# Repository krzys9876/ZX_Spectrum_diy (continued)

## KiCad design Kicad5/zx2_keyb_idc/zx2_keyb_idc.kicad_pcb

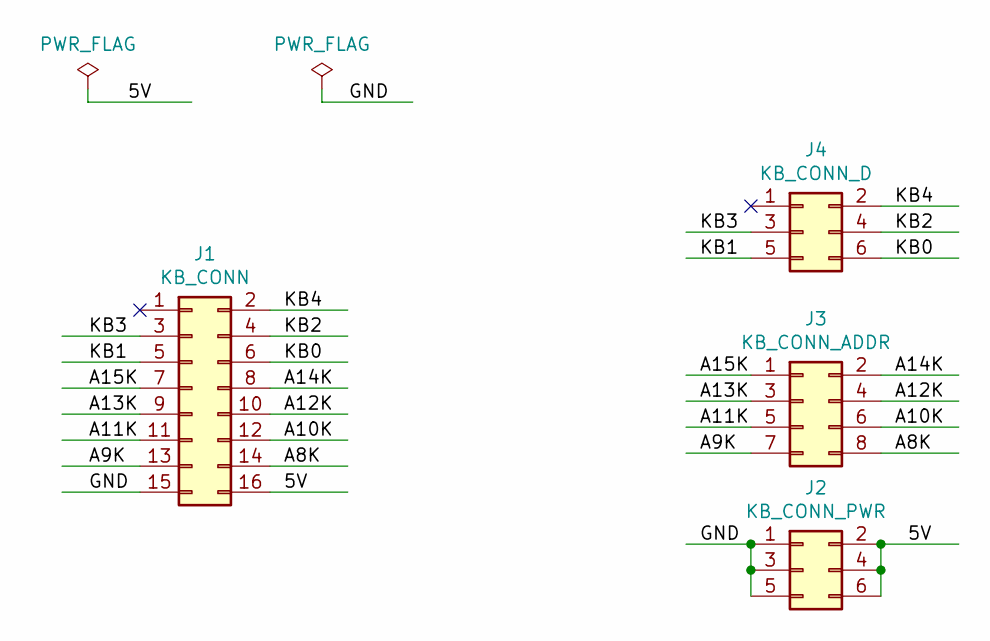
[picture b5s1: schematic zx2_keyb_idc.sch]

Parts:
J1: KB_CONN; PinHeader_2x08_P2.54mm_Vertical_SMD
J2: KB_CONN_PWR; PinHeader_2x03_P2.54mm_Vertical
J3: KB_CONN_ADDR; PinHeader_2x04_P2.54mm_Vertical
J4: KB_CONN_D; PinHeader_2x03_P2.54mm_Vertical

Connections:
/5V: J1.16, J2.2, J2.4, J2.6
/A8K: J1.14, J3.8
/A9K: J1.13, J3.7
/A10K: J1.12, J3.6
/A11K: J1.11, J3.5
/A12K: J1.10, J3.4
/A13K: J1.9, J3.3
/A14K: J1.8, J3.2
/A15K: J1.7, J3.1
/GND: J1.15, J2.1, J2.3, J2.5
/KB0: J1.6, J4.6
/KB1: J1.5, J4.5
/KB2: J1.4, J4.4
/KB3: J1.3, J4.3
/KB4: J1.2, J4.2

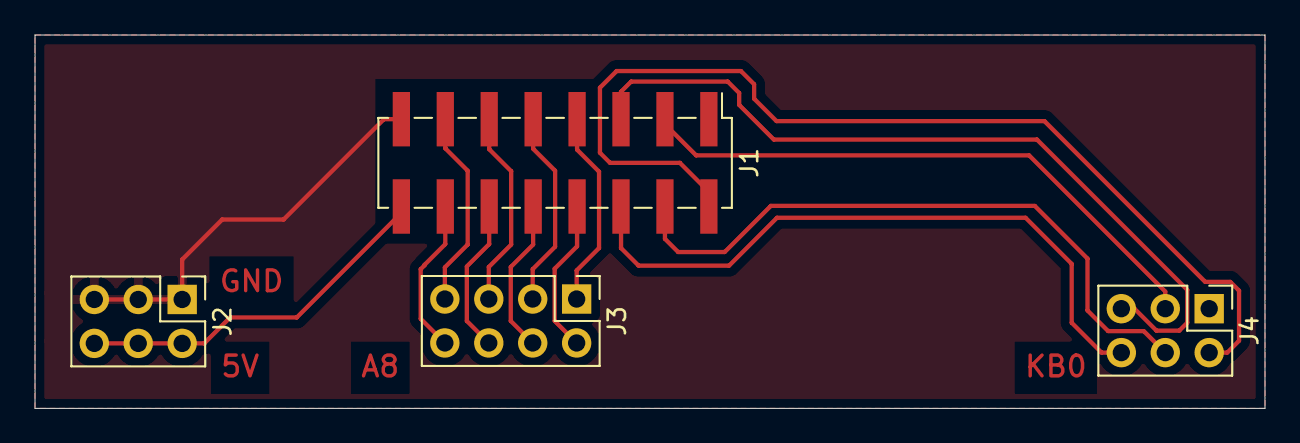
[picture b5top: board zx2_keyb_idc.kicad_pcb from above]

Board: 2 copper layers, 71.1 x 21.6 mm, 4 parts (0 on the bottom side), 15 nets.

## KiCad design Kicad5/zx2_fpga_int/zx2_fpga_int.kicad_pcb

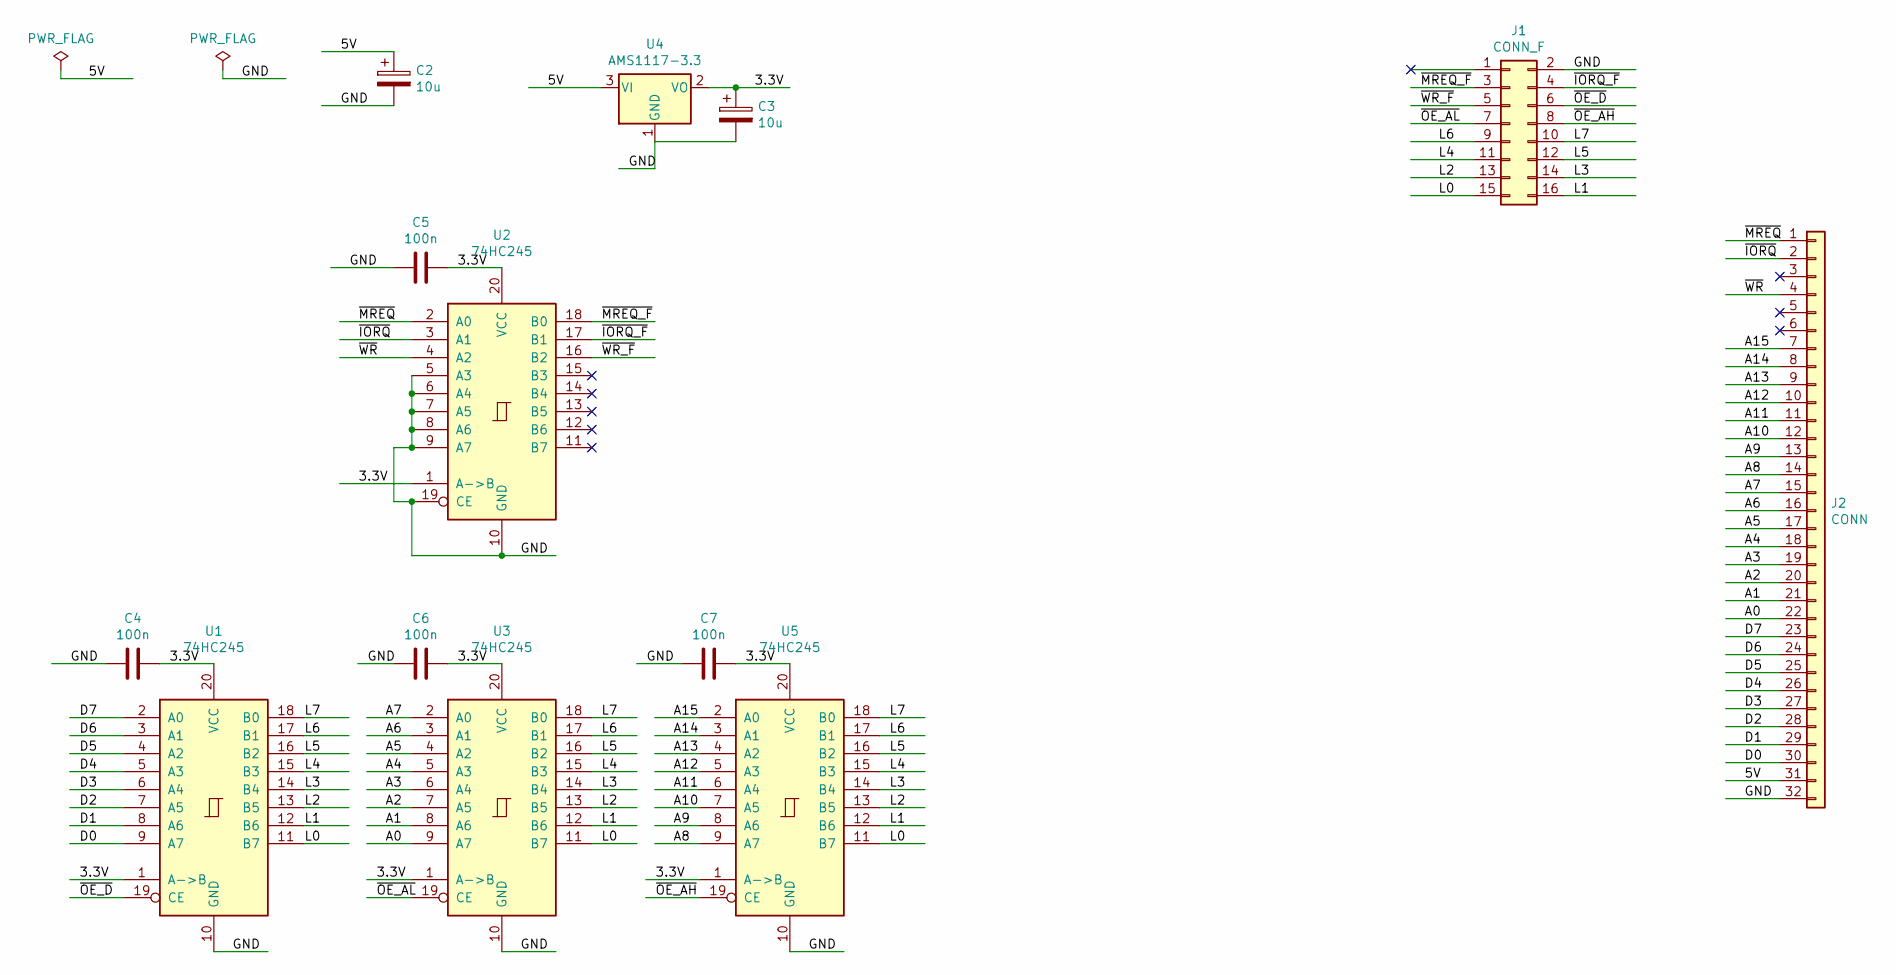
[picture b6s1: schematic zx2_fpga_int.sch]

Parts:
C2, C3: 10u; C_1210_3225Metric
C4, C5, C6, C7: 100n; C_1206_3216Metric
J1: CONN_F; PinHeader_2x08_P2.54mm_Vertical
J2: CONN; PinHeader_1x32_P2.54mm_Horizontal
U1, U2, U3, U5: 74HC245; SO-20_12.8x7.5mm_P1.27mm
U4: AMS1117-3.3; SOT-223-3_TabPin2

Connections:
/3.3V: C3.1, C4.1, C5.1, C6.1, C7.1, U1.1 (A->B), U1.20 (VCC), U2.1 (A->B), U2.20 (VCC), U3.1 (A->B), U3.20 (VCC), U4.2 (VO), U5.1 (A->B), U5.20 (VCC)
/5V: C2.1, J2.31, U4.3 (VI)
/A0: J2.22, U3.9 (A7)
/A1: J2.21, U3.8 (A6)
/A2: J2.20, U3.7 (A5)
/A3: J2.19, U3.6 (A4)
/A4: J2.18, U3.5 (A3)
/A5: J2.17, U3.4 (A2)
/A6: J2.16, U3.3 (A1)
/A7: J2.15, U3.2 (A0)
/A8: J2.14, U5.9 (A7)
/A9: J2.13, U5.8 (A6)
/A10: J2.12, U5.7 (A5)
/A11: J2.11, U5.6 (A4)
/A12: J2.10, U5.5 (A3)
/A13: J2.9, U5.4 (A2)
/A14: J2.8, U5.3 (A1)
/A15: J2.7, U5.2 (A0)
/D0: J2.30, U1.9 (A7)
/D1: J2.29, U1.8 (A6)
/D2: J2.28, U1.7 (A5)
/D3: J2.27, U1.6 (A4)
/D4: J2.26, U1.5 (A3)
/D5: J2.25, U1.4 (A2)
/D6: J2.24, U1.3 (A1)
/D7: J2.23, U1.2 (A0)
/GND: C2.2, C3.2, C4.2, C5.2, C6.2, C7.2, J1.2, J2.32, U1.10 (GND), U2.5 (A3), U2.6 (A4), U2.7 (A5), U2.8 (A6), U2.9 (A7), U2.10 (GND), U2.19 (CE), U3.10 (GND), U4.1 (GND), U5.10 (GND)
/L0: J1.15, U1.11 (B7), U3.11 (B7), U5.11 (B7)
/L1: J1.16, U1.12 (B6), U3.12 (B6), U5.12 (B6)
/L2: J1.13, U1.13 (B5), U3.13 (B5), U5.13 (B5)
/L3: J1.14, U1.14 (B4), U3.14 (B4), U5.14 (B4)
/L4: J1.11, U1.15 (B3), U3.15 (B3), U5.15 (B3)
/L5: J1.12, U1.16 (B2), U3.16 (B2), U5.16 (B2)
/L6: J1.9, U1.17 (B1), U3.17 (B1), U5.17 (B1)
/L7: J1.10, U1.18 (B0), U3.18 (B0), U5.18 (B0)
/~IORQ: J2.2, U2.3 (A1)
/~IORQ_F: J1.4, U2.17 (B1)
/~MREQ: J2.1, U2.2 (A0)
/~MREQ_F: J1.3, U2.18 (B0)
/~OE_AH: J1.8, U5.19 (CE)
/~OE_AL: J1.7, U3.19 (CE)
/~OE_D: J1.6, U1.19 (CE)
/~WR: J2.4, U2.4 (A2)
/~WR_F: J1.5, U2.16 (B2)

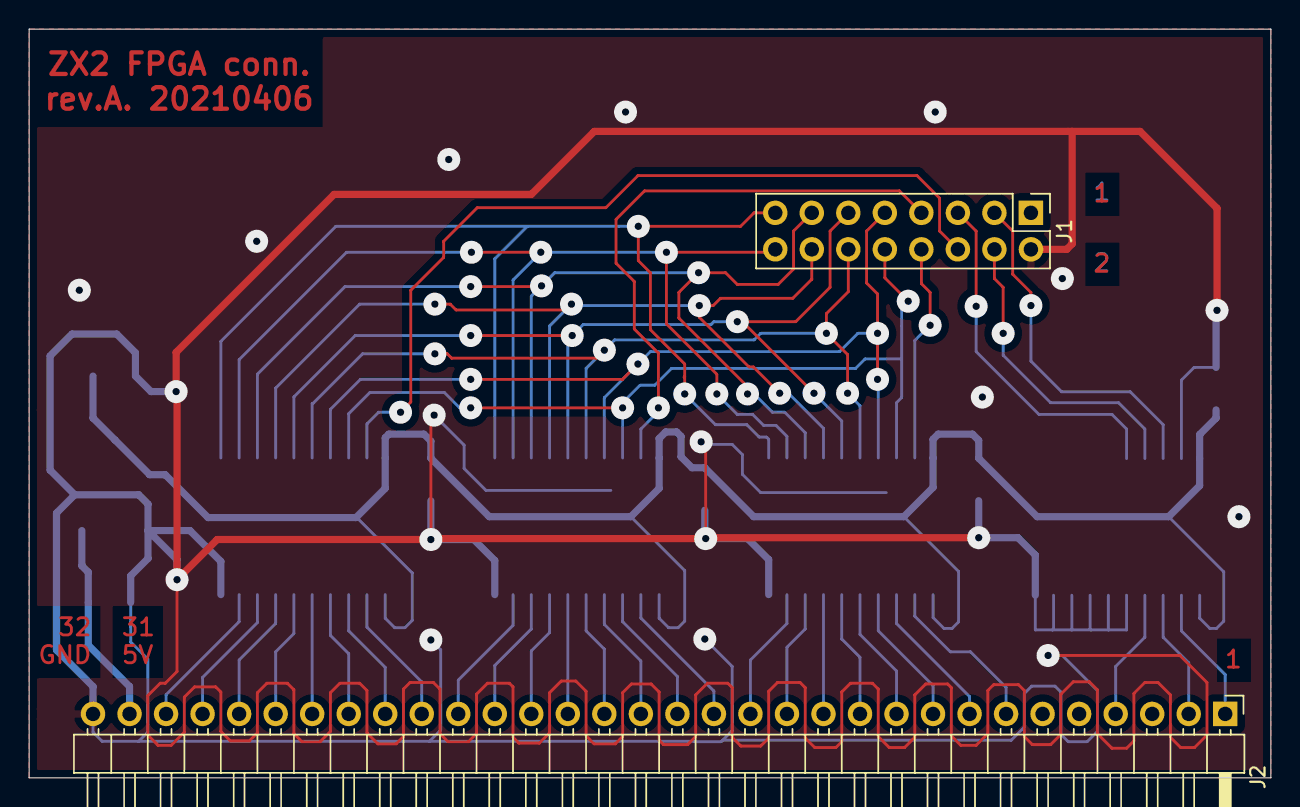
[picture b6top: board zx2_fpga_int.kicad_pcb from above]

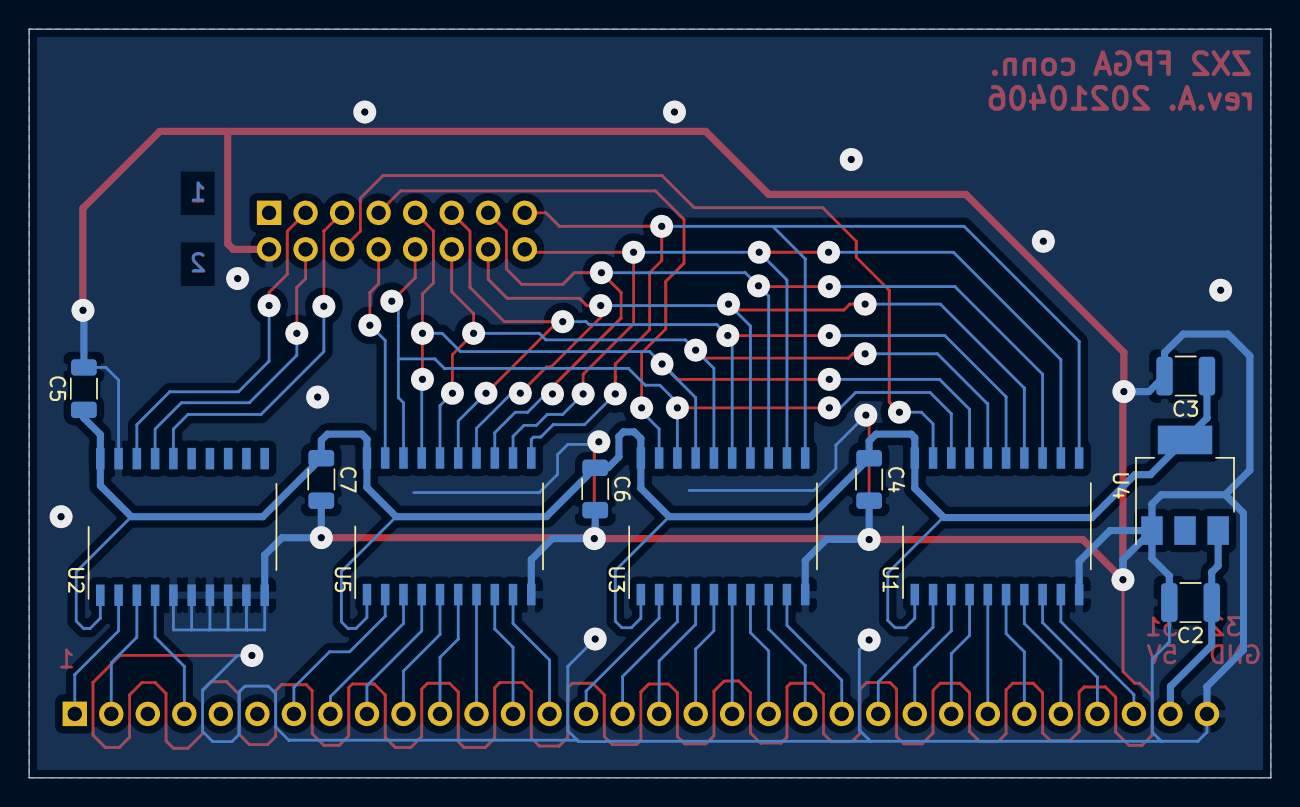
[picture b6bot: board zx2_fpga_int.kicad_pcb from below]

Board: 2 copper layers, 86.4 x 52.1 mm, 13 parts (11 on the bottom side), 44 nets.

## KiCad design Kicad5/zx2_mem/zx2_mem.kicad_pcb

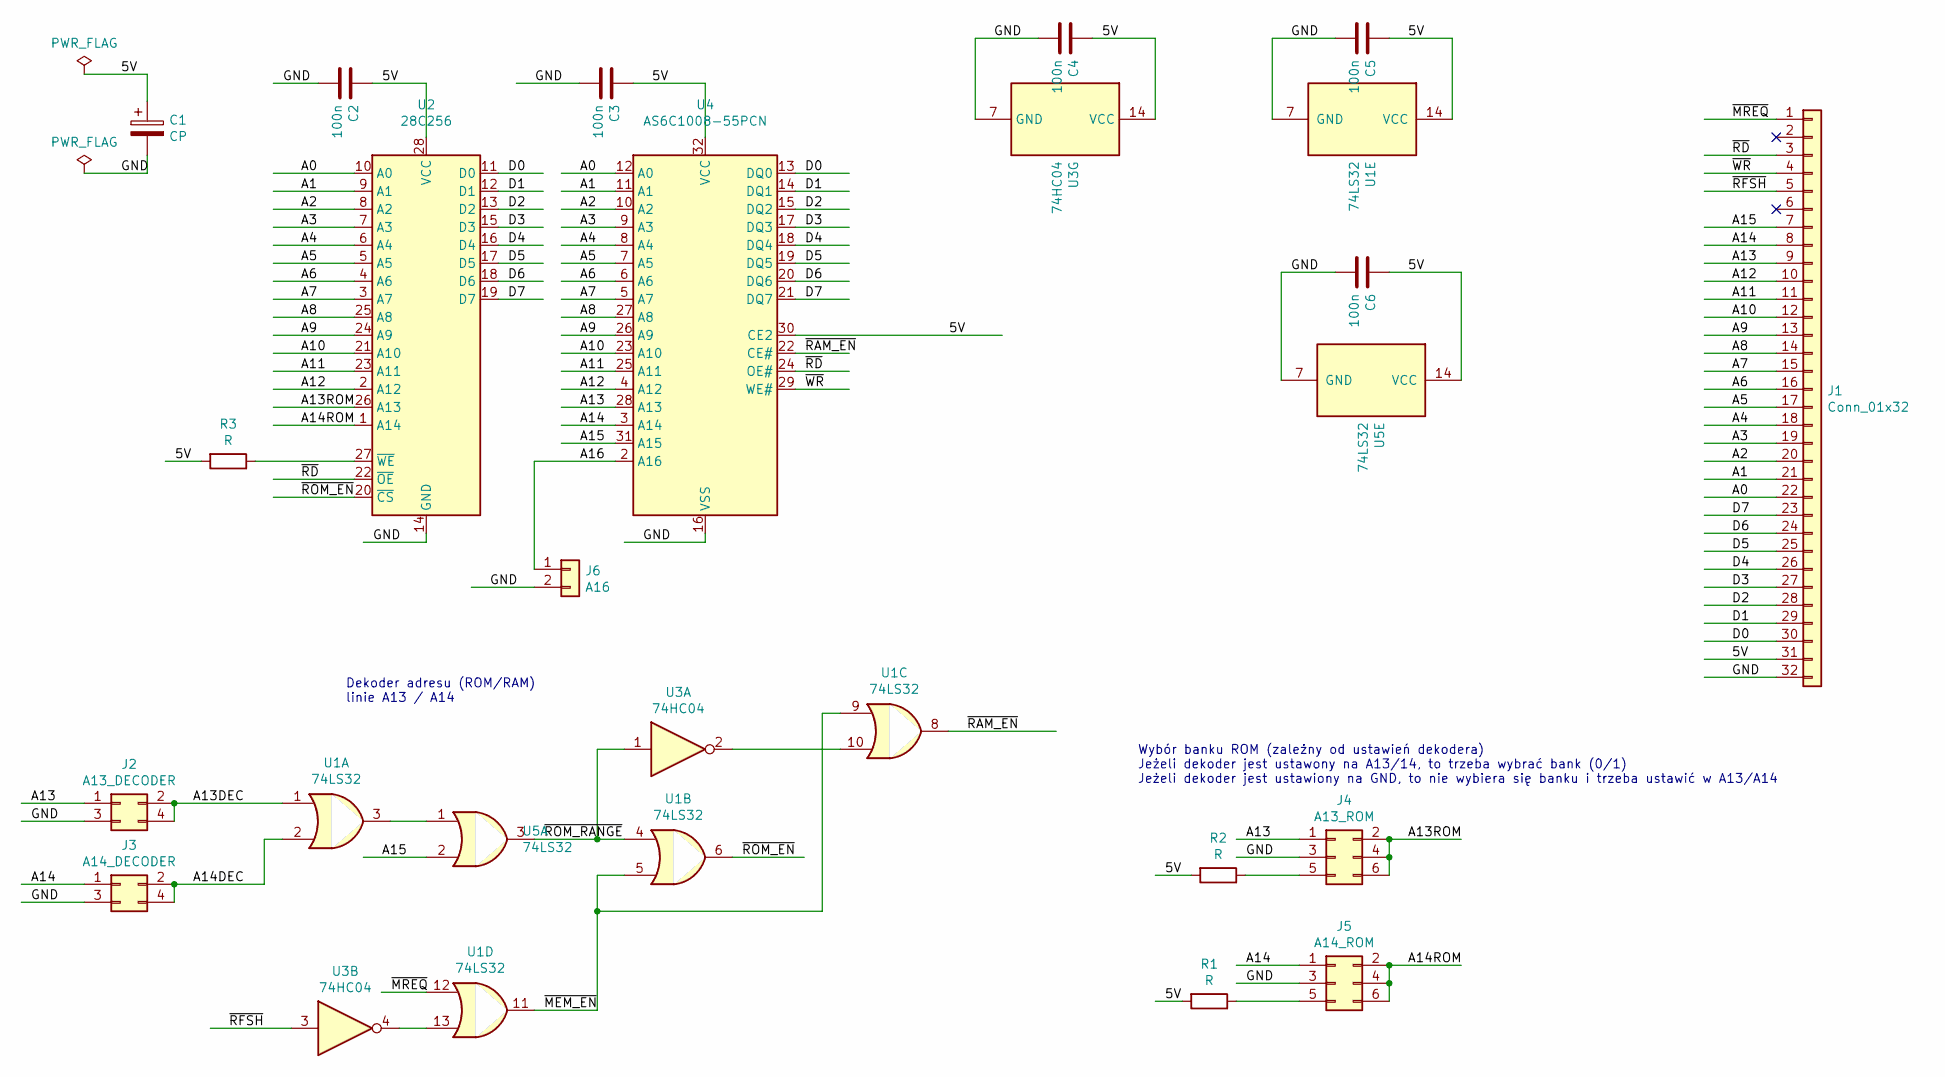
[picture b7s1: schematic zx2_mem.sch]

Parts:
C1: CP; C_1210_3225Metric
C2, C3, C4, C5, C6: 100n; C_1206_3216Metric
J1: Conn_01x32; PinHeader_1x32_P2.54mm_Horizontal
J2: A13_DECODER; PinHeader_2x02_P2.54mm_Vertical
J3: A14_DECODER; PinHeader_2x02_P2.54mm_Vertical
J4: A13_ROM; PinHeader_2x03_P2.54mm_Vertical
J5: A14_ROM; PinHeader_2x03_P2.54mm_Vertical
J6: A16; PinHeader_1x02_P2.54mm_Vertical
R1, R2, R3: R; R_0805_2012Metric
U1, U5: 74LS32; DIP-14_W7.62mm
U2: 28C256; DIP-28_W15.24mm
U3: 74HC04; DIP-14_W7.62mm
U4: AS6C1008-55PCN; DIP-32_W15.24mm

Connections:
/5V: C1.1, C2.1, C3.1, C4.1, C5.1, C6.1, J1.31, R1.2, R2.2, R3.2, U1.14 (VCC), U2.28 (VCC), U3.14 (VCC), U4.30 (CE2), U4.32 (VCC), U5.14 (VCC)
/A0: J1.22, U2.10 (A0), U4.12 (A0)
/A1: J1.21, U2.9 (A1), U4.11 (A1)
/A2: J1.20, U2.8 (A2), U4.10 (A2)
/A3: J1.19, U2.7 (A3), U4.9 (A3)
/A4: J1.18, U2.6 (A4), U4.8 (A4)
/A5: J1.17, U2.5 (A5), U4.7 (A5)
/A6: J1.16, U2.4 (A6), U4.6 (A6)
/A7: J1.15, U2.3 (A7), U4.5 (A7)
/A8: J1.14, U2.25 (A8), U4.27 (A8)
/A9: J1.13, U2.24 (A9), U4.26 (A9)
/A10: J1.12, U2.21 (A10), U4.23 (A10)
/A11: J1.11, U2.23 (A11), U4.25 (A11)
/A12: J1.10, U2.2 (A12), U4.4 (A12)
/A13: J1.9, J2.1, J4.1, U4.28 (A13)
/A13DEC: J2.2, J2.4, U1.1
/A13ROM: J4.2, J4.4, J4.6, U2.26 (A13)
/A14: J1.8, J3.1, J5.1, U4.3 (A14)
/A14DEC: J3.2, J3.4, U1.2
/A14ROM: J5.2, J5.4, J5.6, U2.1 (A14)
/A15: J1.7, U4.31 (A15), U5.2
/A16: J6.1, U4.2 (A16)
/D0: J1.30, U2.11 (D0), U4.13 (DQ0)
/D1: J1.29, U2.12 (D1), U4.14 (DQ1)
/D2: J1.28, U2.13 (D2), U4.15 (DQ2)
/D3: J1.27, U2.15 (D3), U4.17 (DQ3)
/D4: J1.26, U2.16 (D4), U4.18 (DQ4)
/D5: J1.25, U2.17 (D5), U4.19 (DQ5)
/D6: J1.24, U2.18 (D6), U4.20 (DQ6)
/D7: J1.23, U2.19 (D7), U4.21 (DQ7)
/GND: C1.2, C2.2, C3.2, C4.2, C5.2, C6.2, J1.32, J2.3, J3.3, J4.3, J5.3, J6.2, U1.7 (GND), U2.14 (GND), U3.7 (GND), U4.16 (VSS), U5.7 (GND)
/~MEM_EN: U1.5, U1.9, U1.11
/~MREQ: J1.1, U1.12
/~RAM_EN: U1.8, U4.22 (CE#)
/~RD: J1.3, U2.22 (~OE), U4.24 (OE#)
/~RFSH: J1.5, U3.3
/~ROM_EN: U1.6, U2.20 (~CS)
/~ROM_RANGE: U1.4, U3.1, U5.3
/~WR: J1.4, U4.29 (WE#)
unnamed: J4.5, R2.1
unnamed: J5.5, R1.1
unnamed: R3.1, U2.27 (~WE)
unnamed: U1.3, U5.1
unnamed: U1.10, U3.2
unnamed: U1.13, U3.4

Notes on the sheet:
Dekoder adresu (ROM/RAM) linie A13 / A14
Wybór banku ROM (zależny od ustawień dekodera) Jeżeli dekoder jest ustawony na A13/14, to trzeba wybrać bank (0/1) Jeżeli dekoder jest ustawiony na GND, to nie wybiera się banku i trzeba ustawić w A13/A14

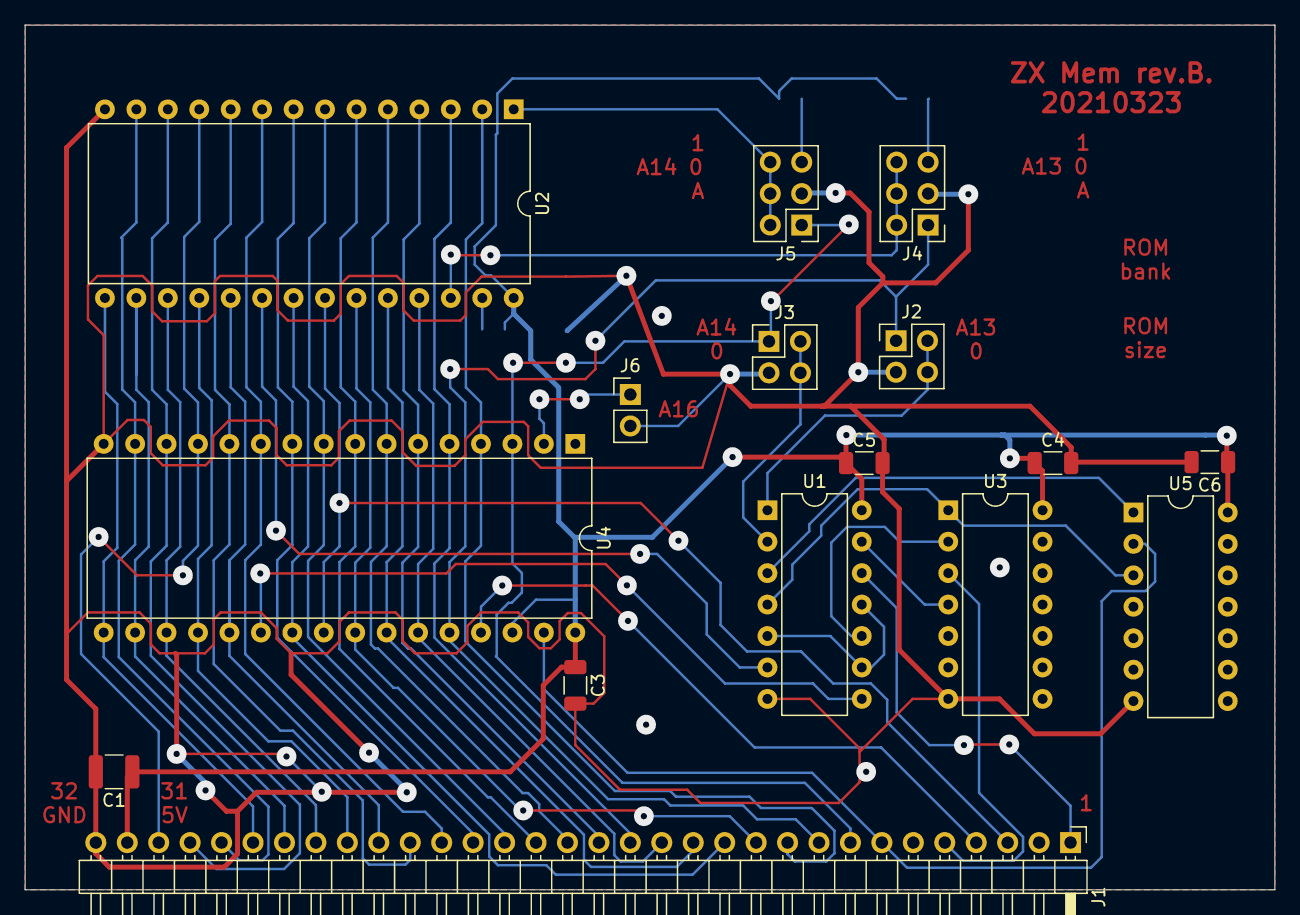
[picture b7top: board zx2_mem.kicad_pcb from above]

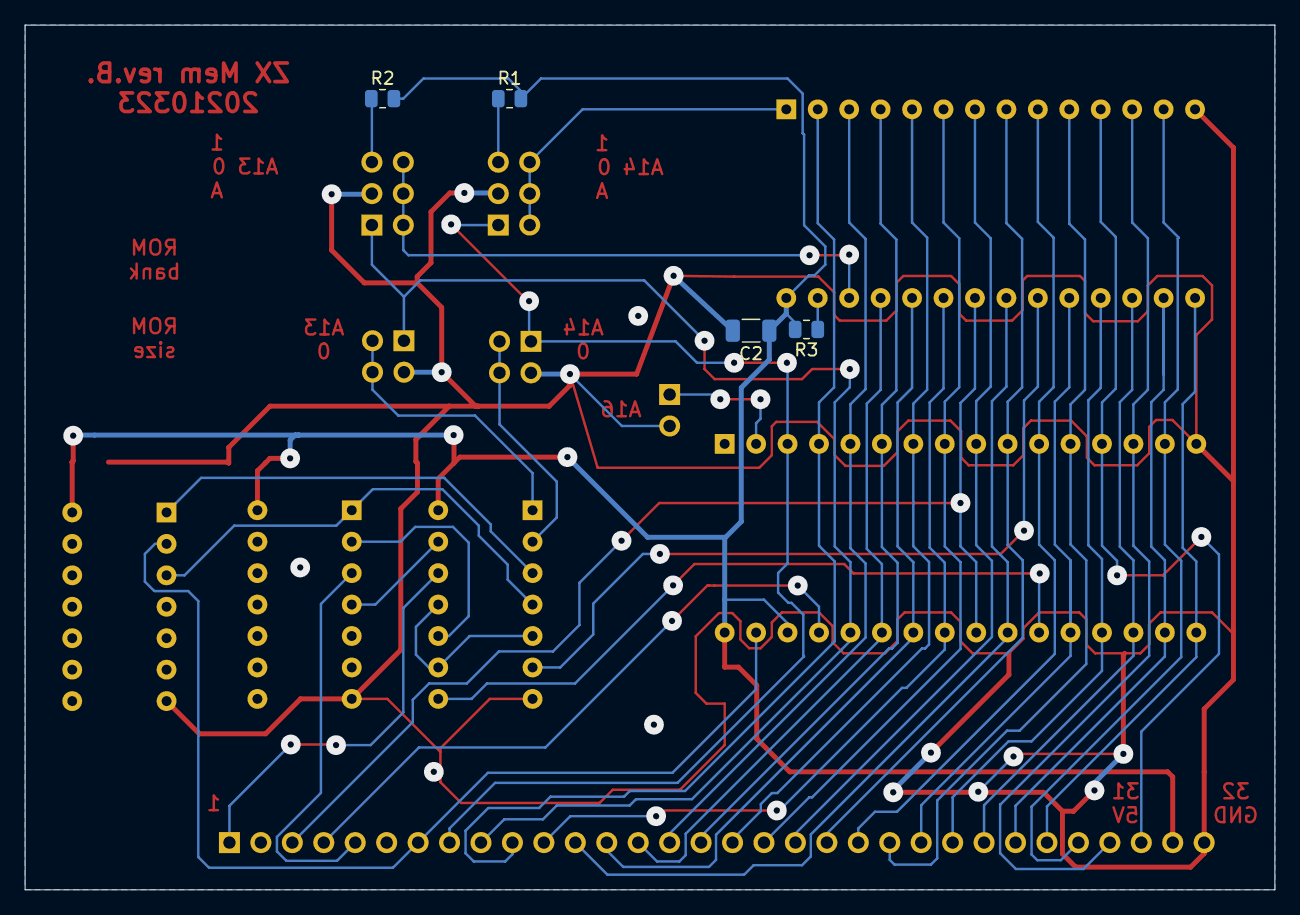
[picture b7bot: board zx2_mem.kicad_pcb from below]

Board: 2 copper layers, 101.0 x 69.8 mm, 20 parts (4 on the bottom side), 45 nets.

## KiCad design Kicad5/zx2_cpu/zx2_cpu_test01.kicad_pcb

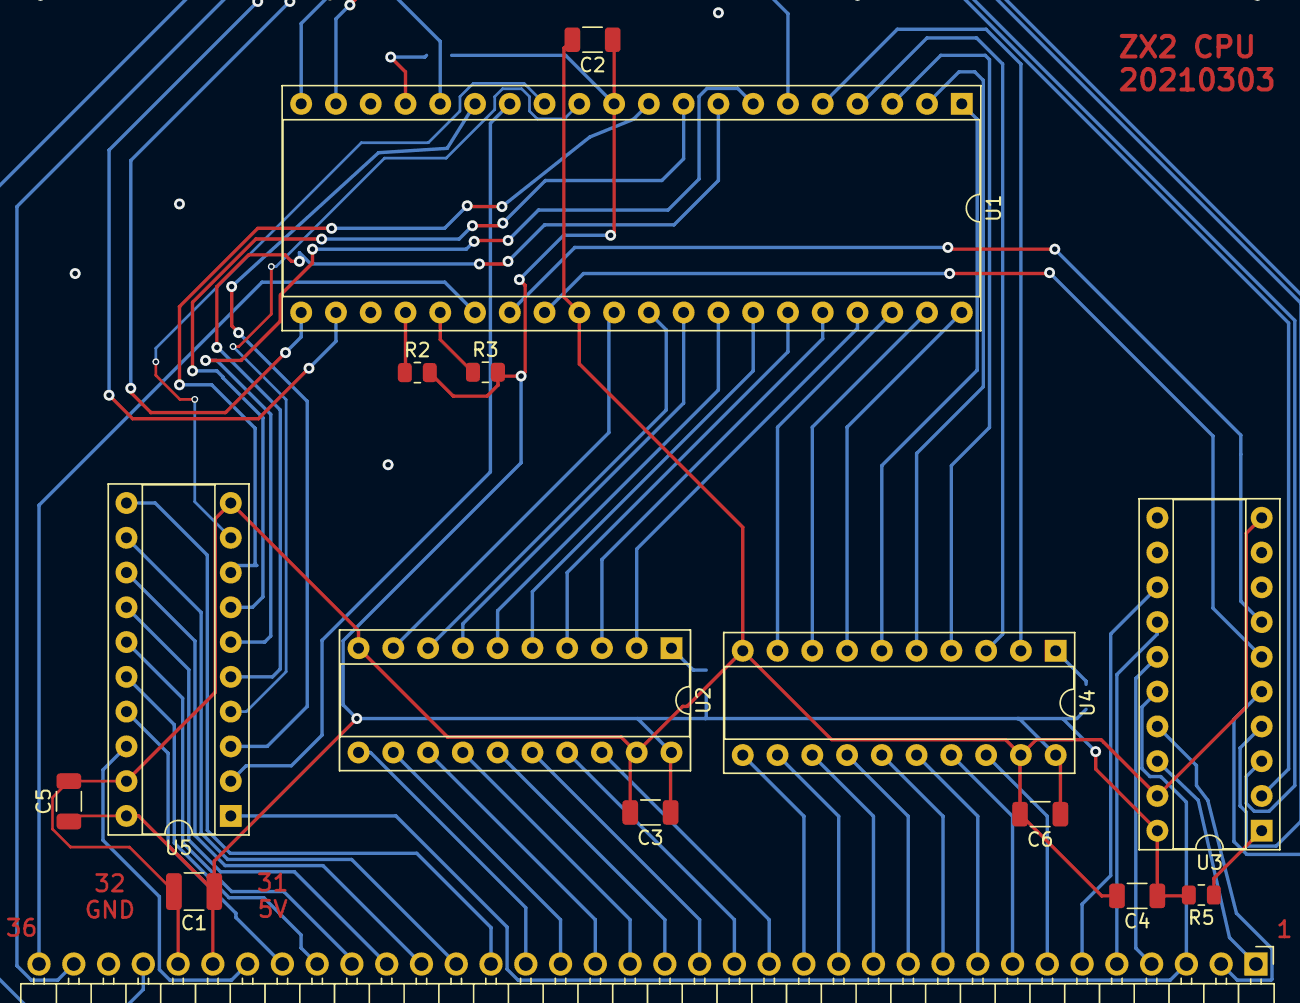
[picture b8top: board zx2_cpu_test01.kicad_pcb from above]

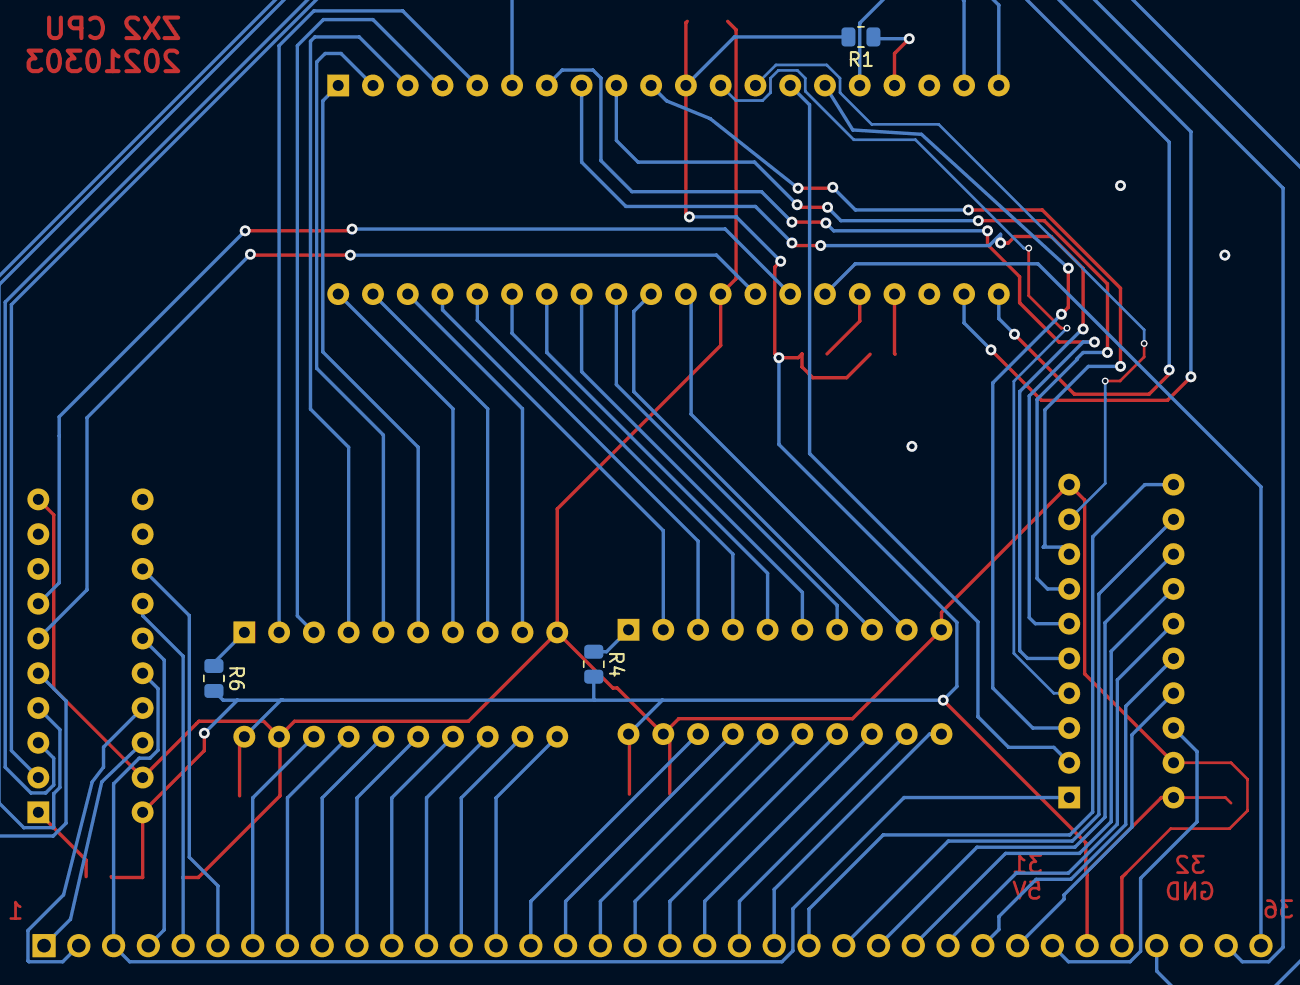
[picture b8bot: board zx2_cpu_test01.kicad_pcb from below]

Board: 2 copper layers, 18 parts (3 on the bottom side), 71 nets.

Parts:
C1: CP; C_1210_3225Metric
C2, C3, C4, C5, C6: 100n; C_1206_3216Metric
J1: Conn_01x36; PinHeader_1x36_P2.54mm_Horizontal
R1, R2, R3, R4, R5, R6: R; R_0805_2012Metric
U1: Z80CPU; DIP-40_W15.24mm_Socket
U2, U3, U4, U5: 74HC245; DIP-20_W7.62mm_Socket

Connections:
/5V: C1.1, C2.1, C3.1, C4.1, C5.1, C6.1, J1.31, R1.2, R2.2, R3.2, R4.2, R5.2, R6.2, U1.11, U2.20, U3.20, U4.20, U5.20
/A0: J1.22, U2.11
/A0CPU: U1.30, U2.9
/A1: J1.21, U2.12
/A1CPU: U1.31, U2.8
/A2: J1.20, U2.13
/A2CPU: U1.32, U2.7
/A3: J1.19, U2.14
/A3CPU: U1.33, U2.6
/A4: J1.18, U2.15
/A4CPU: U1.34, U2.5
/A5: J1.17, U2.16
/A5CPU: U1.35, U2.4
/A6: J1.16, U2.17
/A6CPU: U1.36, U2.3
/A7: J1.15, U2.18
/A7CPU: U1.37, U2.2
/A8: J1.14, U4.11
/A8CPU: U1.38, U4.9
/A9: J1.13, U4.12
/A9CPU: U1.39, U4.8
/A10: J1.12, U4.13
/A10CPU: U1.40, U4.7
/A11: J1.11, U4.14
/A11CPU: U1.1, U4.6
/A12: J1.10, U4.15
/A12CPU: U1.2, U4.5
/A13: J1.9, U4.16
/A13CPU: U1.3, U4.4
/A14: J1.8, U4.17
/A14CPU: U1.4, U4.3
/A15: J1.7, U4.18
/A15CPU: U1.5, U4.2
/CLK: J1.33, U1.6
/D0: J1.30, U5.18
/D0CPU: U1.14, U5.2
/D1: J1.29, U5.17
/D1CPU: U1.15, U5.3
/D2: J1.28, U5.16
/D2CPU: U1.12, U5.4
/D3: J1.27, U5.15
/D3CPU: U1.8, U5.5
/D4: J1.26, U5.14
/D4CPU: U1.7, U5.6
/D5: J1.25, U5.13
/D5CPU: U1.9, U5.7
/D6: J1.24, U5.12
/D6CPU: U1.10, U5.8
/D7: J1.23, U5.11
/D7CPU: U1.13, U5.9
/GND: C1.2, C2.2, C3.2, C4.2, C5.2, C6.2, J1.32, U1.29, U2.10, U2.19, U3.10, U3.19, U4.10, U4.19, U5.10, U5.19
/~INT: J1.35, U1.16
/~IORQ: J1.2, U3.17
/~IORQCPU: U1.20, U3.3
/~M1: J1.6, U3.13
/~M1CPU: U1.27, U3.7
/~MREQ: J1.1, U3.18
/~MREQCPU: U1.19, U3.2
/~RD: J1.3, U3.16, U5.1
/~RDCPU: U1.21, U3.4
/~RESET: J1.36, U1.26
/~RFSH: J1.5, U3.14
/~RFSHCPU: U1.28, U3.6
/~WR: J1.4, U3.15
/~WRCPU: U1.22, U3.5
unnamed: R1.1, U1.17
unnamed: R2.1, U1.24
unnamed: R3.1, U1.25
unnamed: R4.1, U2.1
unnamed: R5.1, U3.1
unnamed: R6.1, U4.1

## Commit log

2021-10-03 Initial commit - copy from local
